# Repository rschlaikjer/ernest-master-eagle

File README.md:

# Ernest Master Node Schematics
Eagle files for Ernest base node

[Master Project Repo](https://github.com/rschlaikjer/Ernest)

## What is this
Ernest is the next step of the [ArNest](https://github.com/rschlaikjer/ArNest),
and takes it from a single-location thermostat to a many node system consisting
of a base station and one or more smaller nodes that collect and report
atmospheric data to the base. This way the system can monitor multiple rooms, as
well as the outside conditions.

These EAGLE files show the schematic for the master node, which collects data
transmitted by the slaves (as well as from its own onboard sensors) and sends
it to the server. This node also controls the relay for the furnace, if you
are using this as a thermostat.

This board is designed to be run over PoE, using a Silvertel AG9000 or similar
module, as is used on the PoE version of the Arduino ethernet.

For the code to run on the master node,
[see here](https://github.com/rschlaikjer/ernest-master-code).

## Parts list
(All prices per unit and approximate)

- ($2.00) Atmega 328P (with arduino-style bootloader)
- ($3.19) USB FTDI programmer
- ($1.50) (Optional) BMP180 breakout board
- ($13.75) (Optional) HIH-6130 humidity sensor
- ($0.98) nrf24L01 wireless transciever
- ($0.39) LM1117 3.3V regulator
- ($0.07) 16 MHz crystal oscillator
- ($0.03) 22pF capacitors
- ($0.08) Momentary reset switch
- ($0.01) 320 Ohm resistors
- ($0.03) LEDs
- ($2.50) RB1-125BHQ1A PoE RJ45 jack
- ($10.64) Ag-9000S (or newer) PoE module

**Total BOM: Approx. $15 per board** + 13.75 for humidity, as well as the cost
of PCB manufacture.

## Pretty Pictures

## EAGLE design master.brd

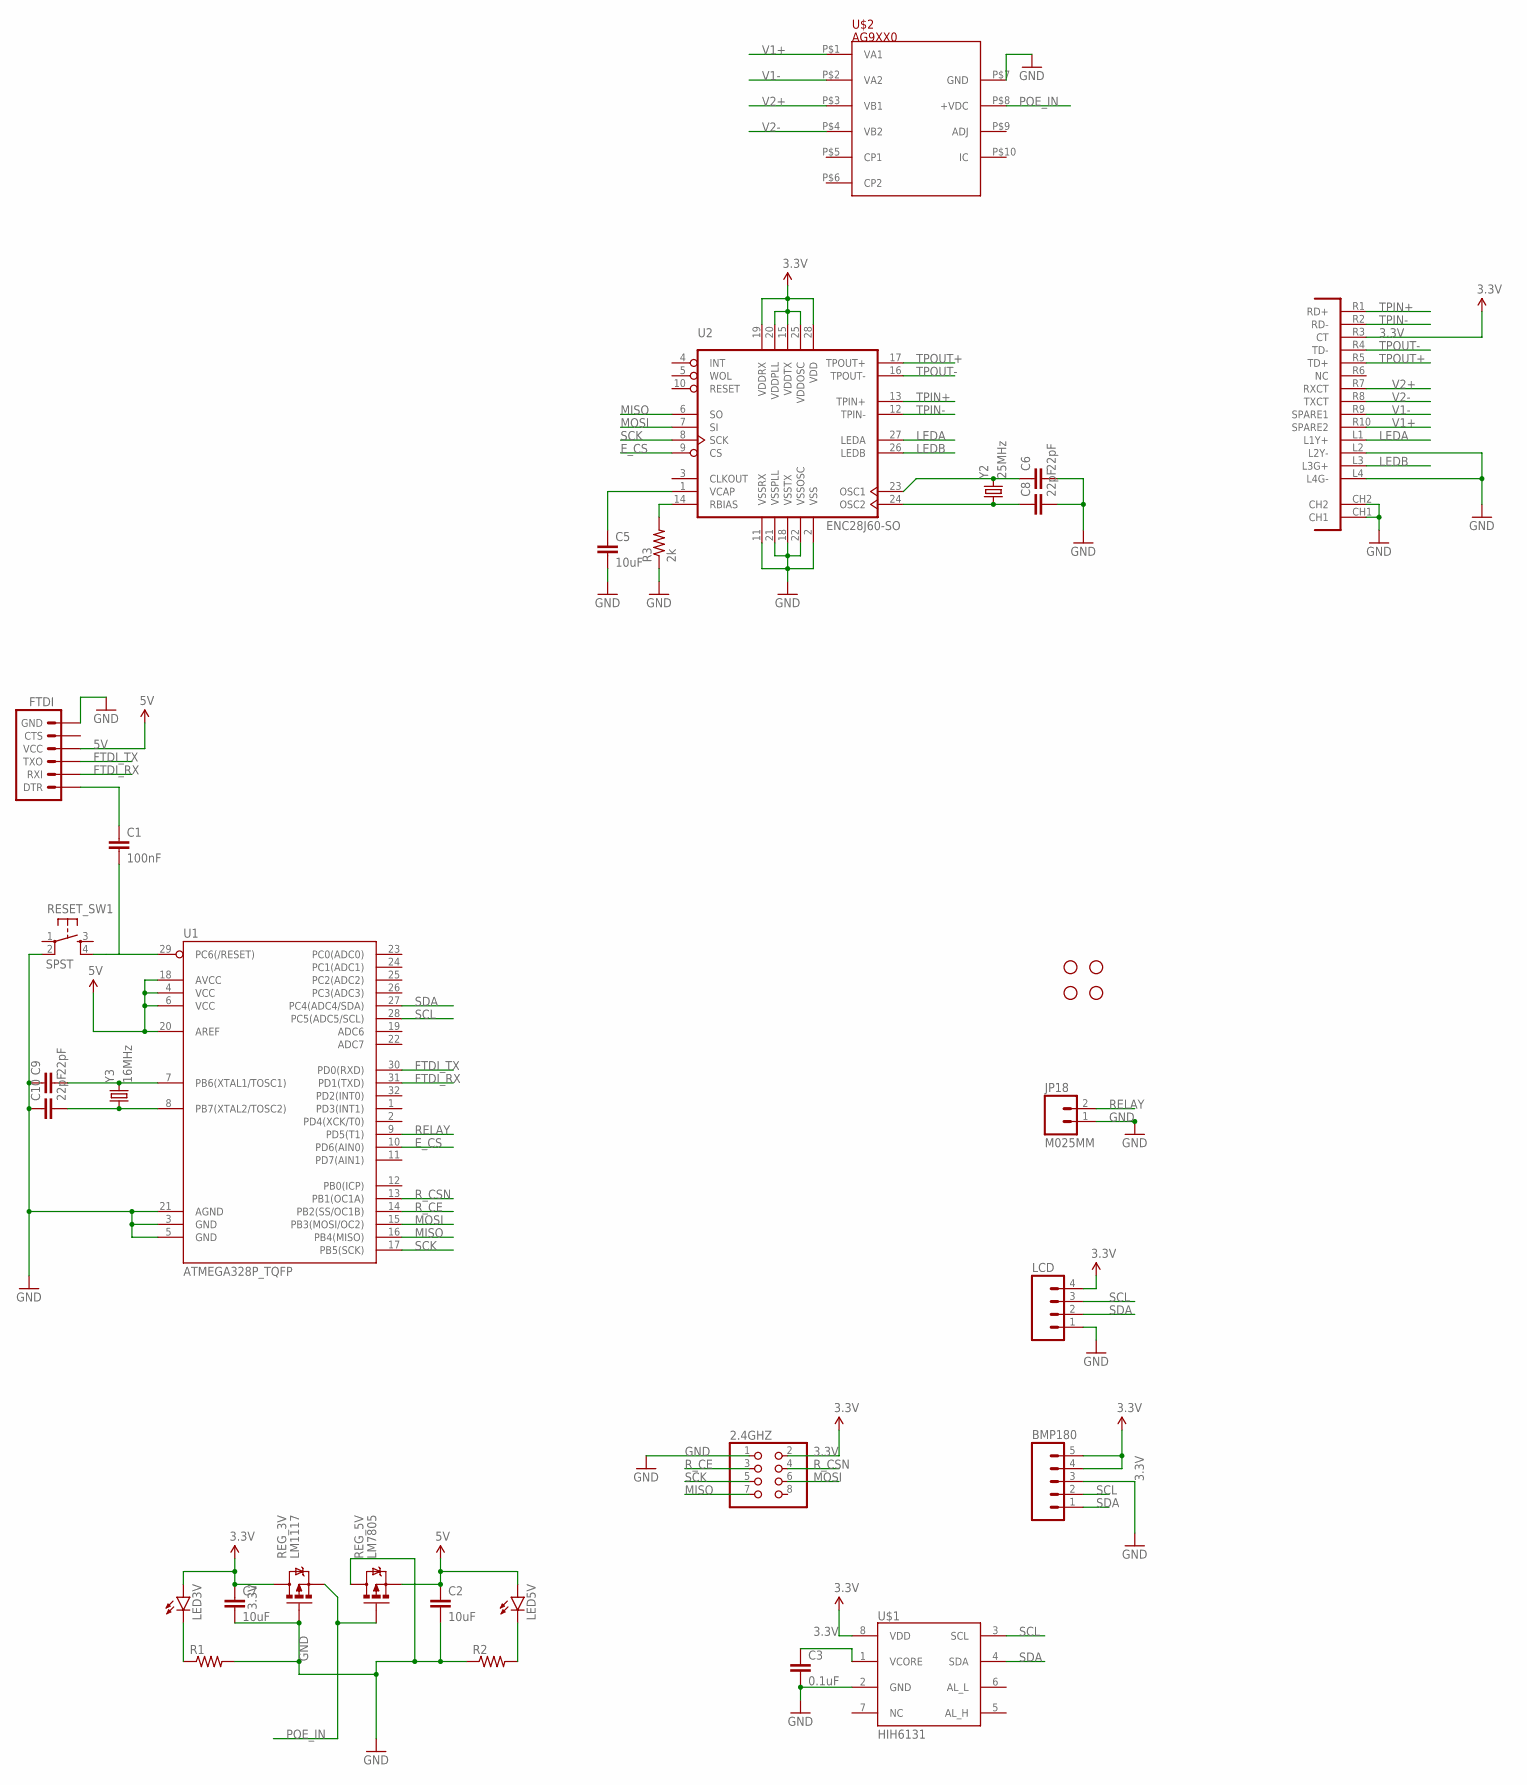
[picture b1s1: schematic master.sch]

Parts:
2.4GHZ: PINHD-2X4; 2X04
BMP180: M05PTH; 1X05
C1: 100nF; CAP-PTH-SMALL
C2, C5, C7: 10uF; CAP-PTH-SMALL
C3: 0.1uF; CAP-PTH-SMALL
C6, C8, C9, C10: 22pF; CAP-PTH-SMALL
FTDI: ARDUINO_SERIAL_PROGRAMPTH; 1X06
JP18: M025MM; SCREWTERMINAL-5MM-2
LCD: M04PTH; 1X04
LED3V, LED5V: LED3MM
R1, R2: RESISTORPTH-1/4W-VERT; AXIAL-0.1
R3: 2k; AXIAL-0.1
REG_3V: LM1117; TO220V
REG_5V: LM7805; TO220V
RESET_SW1: SPST; TAC-SWITCH-PTH
STANDOFF1, STANDOFF2, STANDOFF3, STANDOFF4: STAND-OFF
U1: ATMEGA328P_TQFP; TQFP32-08
U2: ENC28J60-SO; SO28W
U$1: HIH6131; SOIC8
U$2: AG9XX0; AG9000
U$3: POE-RJ45
Y2: 25MHz; HC49US
Y3: 16MHz; HC49US

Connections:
3.3V: 2.4GHZ.2, BMP180.4, BMP180.5, C7.1, LCD.4, LED3V.A, REG_3V.2 (D), U2.15 (VDDTX), U2.19 (VDDRX), U2.20 (VDDPLL), U2.25 (VDDOSC), U2.28 (VDD), U$1.8 (VDD), U$3.R3 (CT)
5V: C2.1, FTDI.4 (VCC), LED5V.A, REG_5V.3 (S), U1.4 (VCC), U1.6 (VCC), U1.18 (AVCC), U1.20 (AREF)
E_CS: U1.10 (PD6(AIN0)), U2.9 (CS)
FTDI_RX: FTDI.2 (RXI), U1.31 (PD1(TXD))
FTDI_TX: FTDI.3 (TXO), U1.30 (PD0(RXD))
GND: 2.4GHZ.1, BMP180.3, C2.2, C3.2, C5.2, C6.2, C7.2, C8.2, C9.1, C10.1, FTDI.6 (GND), JP18.1, LCD.1, R1.P$2 (2), R2.P$1 (1), R3.P$1 (1), REG_3V.1 (G), REG_5V.2 (D), RESET_SW1.2, U1.3 (GND), U1.5 (GND), U1.21 (AGND), U2.2 (VSS), U2.11 (VSSRX), U2.18 (VSSTX), U2.21 (VSSPLL), U2.22 (VSSOSC), U$1.2 (GND), U$2.P$7 (GND), U$3.CH1, U$3.CH2, U$3.L2 (L2Y-), U$3.L4 (L4G-)
LEDA: U2.27 (LEDA), U$3.L1 (L1Y+)
LEDB: U2.26 (LEDB), U$3.L3 (L3G+)
MISO: 2.4GHZ.7, U1.16 (PB4(MISO)), U2.6 (SO)
MOSI: 2.4GHZ.6, U1.15 (PB3(MOSI/OC2)), U2.7 (SI)
unnamed: LED3V.K (C), R1.P$1 (1)
unnamed: LED5V.K (C), R2.P$2 (2)
unnamed: R3.P$2 (2), U2.14 (RBIAS)
unnamed: C5.1, U2.1 (VCAP)
unnamed: C6.1, U2.23 (OSC1), Y2.2
unnamed: C8.1, U2.24 (OSC2), Y2.1
unnamed: C3.1, U$1.1 (VCORE)
unnamed: C9.2, U1.7 (PB6(XTAL1/TOSC1)), Y3.2
unnamed: C10.2, U1.8 (PB7(XTAL2/TOSC2)), Y3.1
unnamed: C1.1, FTDI.1 (DTR)
POE_IN: REG_3V.3 (S), REG_5V.1 (G), U$2.P$8 (+VDC)
RELAY: JP18.2, U1.9 (PD5(T1))
RESET: C1.2, RESET_SW1.4, U1.29 (PC6(/RESET))
R_CE: 2.4GHZ.3, U1.14 (PB2(SS/OC1B))
R_CSN: 2.4GHZ.4, U1.13 (PB1(OC1A))
SCK: 2.4GHZ.5, U1.17 (PB5(SCK)), U2.8 (SCK)
SCL: BMP180.2, LCD.3, U1.28 (PC5(ADC5/SCL)), U$1.3 (SCL)
SDA: BMP180.1, LCD.2, U1.27 (PC4(ADC4/SDA)), U$1.4 (SDA)
TPIN+: U2.13 (TPIN+), U$3.R1 (RD+)
TPIN-: U2.12 (TPIN-), U$3.R2 (RD-)
TPOUT+: U2.17 (TPOUT+), U$3.R5 (TD+)
TPOUT-: U2.16 (TPOUT-), U$3.R4 (TD-)
V1+: U$2.P$1 (VA1), U$3.R10 (SPARE2)
V1-: U$2.P$2 (VA2), U$3.R9 (SPARE1)
V2+: U$2.P$3 (VB1), U$3.R7 (RXCT)
V2-: U$2.P$4 (VB2), U$3.R8 (TXCT)

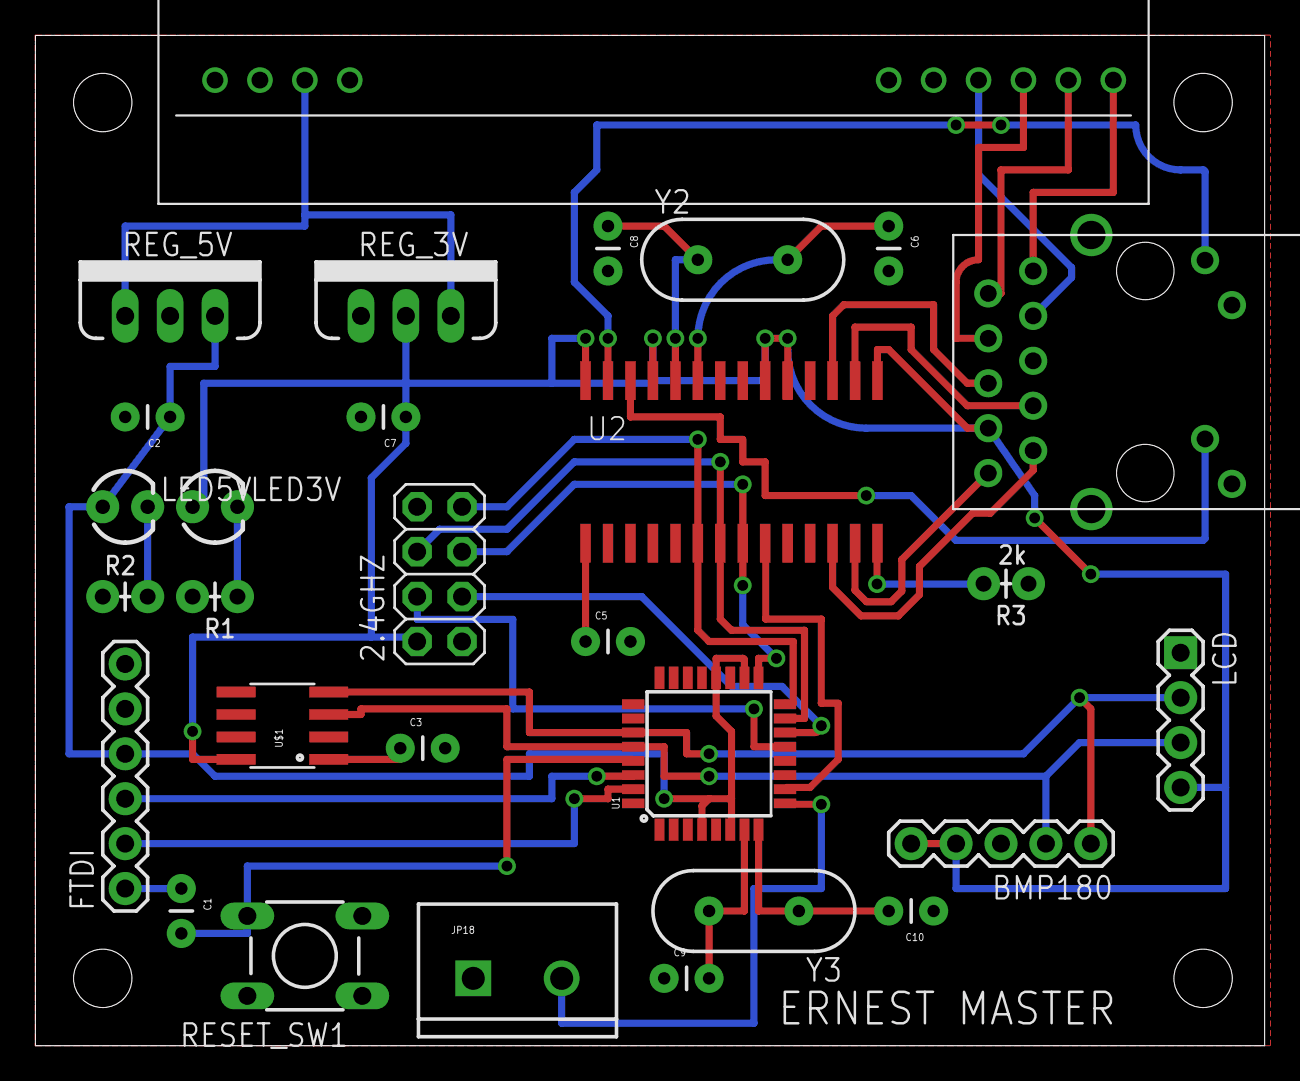
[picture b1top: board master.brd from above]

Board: 2 copper layers, 69.5 x 57.1 mm, 33 parts (0 on the bottom side), 36 nets.

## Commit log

2015-02-27 Fab v1
2015-02-27 Use SMD Atmega
2015-03-08 Fix LM7805 pinout
2015-03-08 Add README
2015-03-08 Tidy schematic

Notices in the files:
parts and their libraries:
SparkFun-Connectors: Licensing: Creative Commons ShareAlike 4.0 International - https://creativecommons.org/licenses/by-sa/4.0
